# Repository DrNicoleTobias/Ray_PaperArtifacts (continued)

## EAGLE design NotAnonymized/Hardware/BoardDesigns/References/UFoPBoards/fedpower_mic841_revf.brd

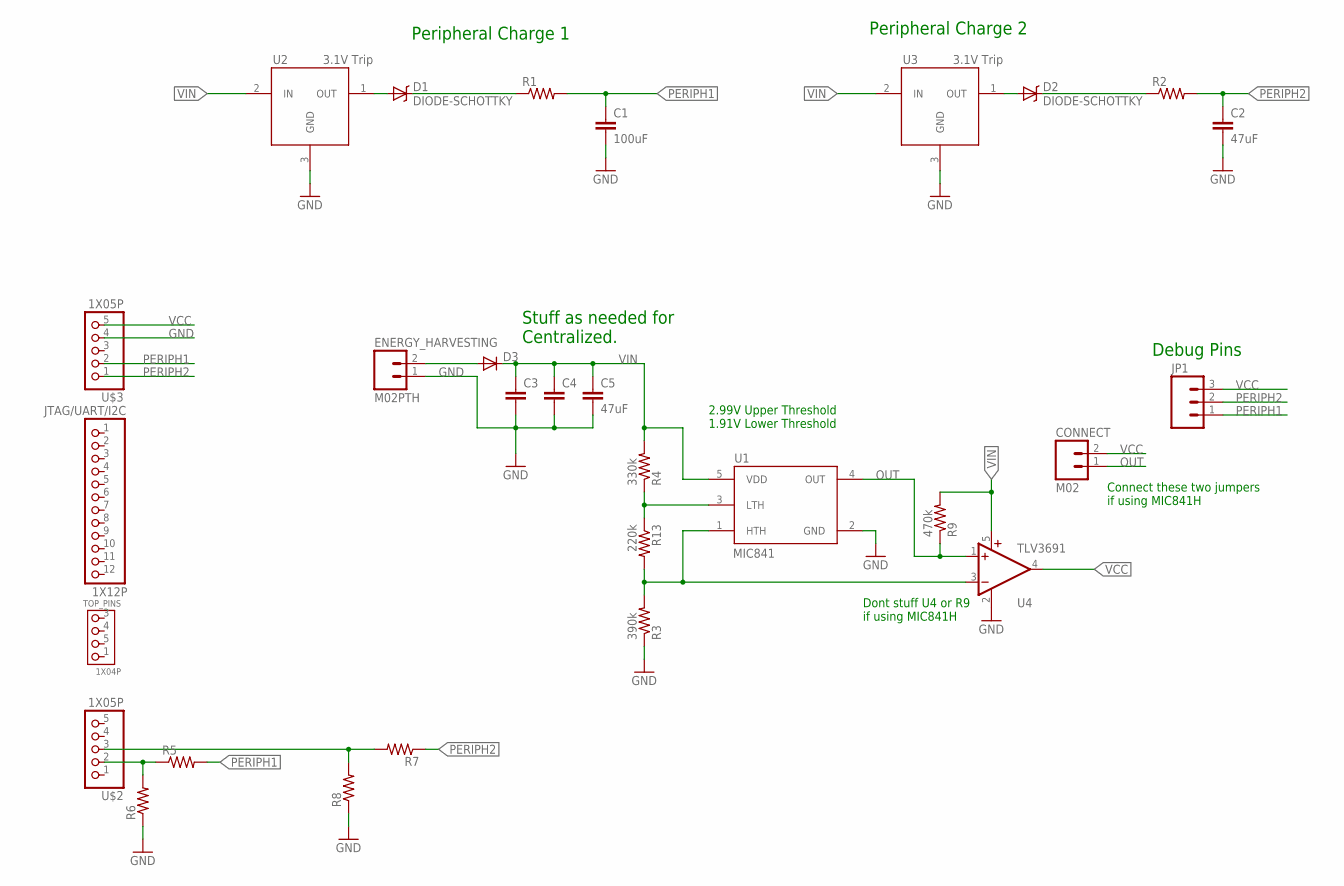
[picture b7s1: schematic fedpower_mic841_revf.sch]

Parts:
C1: 100uF; 0805
C2, C5: 47uF; 0805
C3, C4: 1.0UF-25V-+80/-20(0805); 0805
CONNECT: M02; 1X02-1.27MM
D1, D2: DIODE-SCHOTTKY; SOD-323
D3: DIODESOD; SOD-323
ENERGY_HARVESTING: M02PTH; 1X02
JP1: M03PTH; 1X03
JTAG/UART/I2C: 1X12P
R1, R2, R5, R6, R7, R8: 0.3OHM-1/8W-1%(0805); 0805
R3: 390k; 0805
R4: 330k; 0805
R9: 470k; 0805
R13: 220k; 0805
TOP_PINS: 1X04P
U1: MIC841; SC70-5
U2, U3: 3.1V Trip; SOT-23-5_1PRIMARY
U4: TLV3691; SC70-5
U$2, U$3: 1X05P

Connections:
GND: C1.2, C2.2, C3.2, C4.2, C5.2, ENERGY_HARVESTING.1, R3.1, R6.1, R8.1, U1.2 (GND), U2.3 (GND), U3.3 (GND), U4.2 (GND), U$3.4
unnamed: D1.2 (A), U2.1 (OUT)
unnamed: R4.1, R13.1, U1.3 (LTH)
unnamed: D1.1 (C), R1.1
unnamed: D2.2 (A), U3.1 (OUT)
unnamed: D3.2 (A), ENERGY_HARVESTING.2
unnamed: D2.1 (C), R2.1
unnamed: R3.2, R13.2, U1.1 (HTH), U4.3 (-IN)
OUT: CONNECT.1, R9.1, U1.4 (OUT), U4.1 (+IN)
P1.3/C3: R5.1, R6.2, U$2.2
P1.4/C4: R7.2, R8.2, U$2.3
PERIPH1: C1.1, JP1.1, R1.2, R5.2, U$3.2
PERIPH2: C2.1, JP1.2, R2.2, R7.1, U$3.1
VCC: CONNECT.2, JP1.3, U4.4 (OUT), U$3.5
VIN: C3.1, C4.1, C5.1, D3.1 (C), R4.2, R9.2, U1.5 (VDD), U2.2 (IN), U3.2 (IN), U4.5 (V+)

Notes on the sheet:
Peripheral Charge 1
Peripheral Charge 2
Debug Pins
Stuff as needed for Centralized.
Dont stuff U4 or R9 if using MIC841H
Connect these two jumpers if using MIC841H
2.99V Upper Threshold 1.91V Lower Threshold

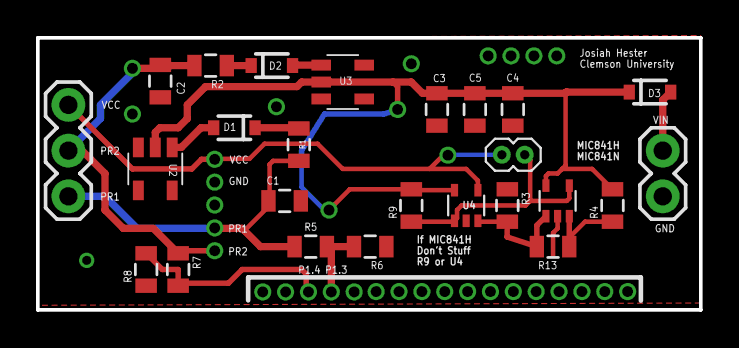
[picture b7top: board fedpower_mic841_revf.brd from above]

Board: 2 copper layers, 36.8 x 15.1 mm, 29 parts (0 on the bottom side), 15 nets.

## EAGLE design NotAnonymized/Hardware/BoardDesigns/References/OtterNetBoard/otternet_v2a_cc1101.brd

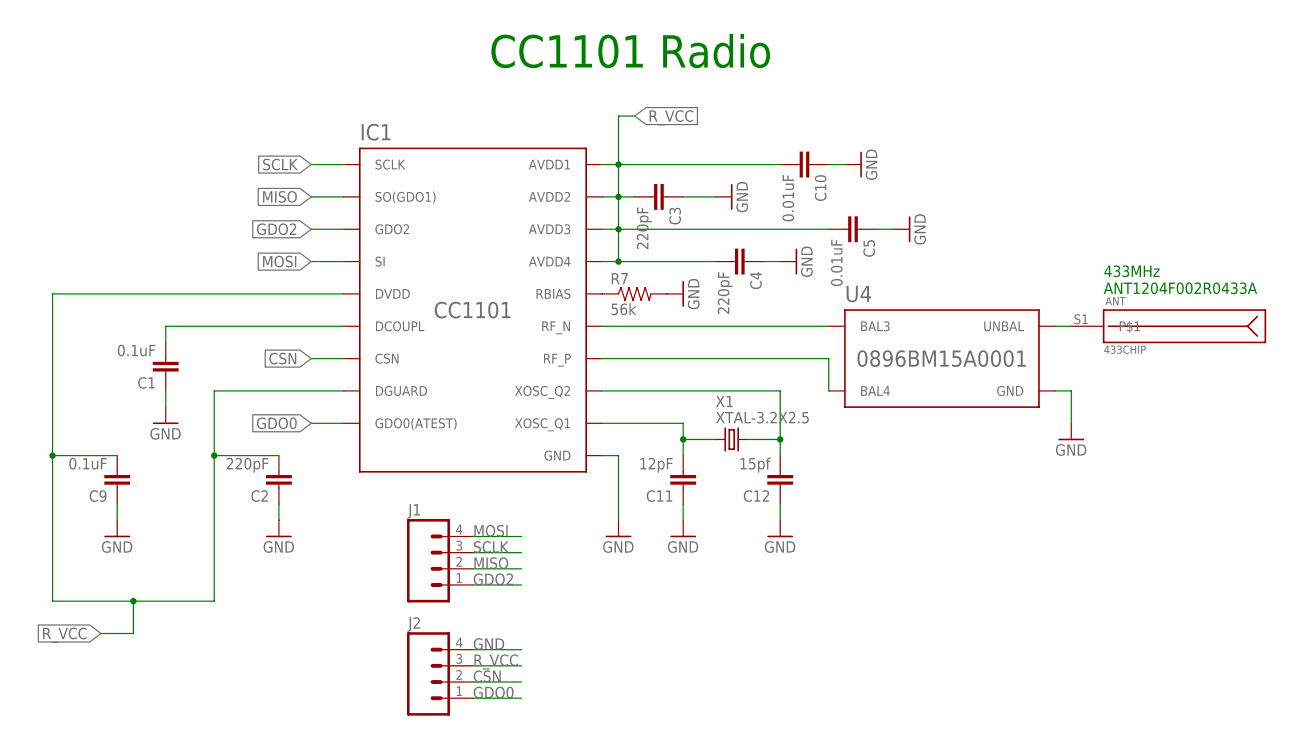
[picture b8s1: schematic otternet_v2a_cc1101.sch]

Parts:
ANT: 433CHIP; ANT-433-USP; MOUSER 603-ANT1204F002R0433
C1, C9: 0.1uF; 0402; MOUSER 581-530L104KT16T
C2, C3, C4: 220pF; 0402; MOUSER 605-500X07W221MV4T
C5, C10: 0.01uF; 0402; MOUSER 80-C0402T103K5RCL
C11: 12pF; 0402; MOUSER 581-04025U120FAT2A
C12: 15pf; 0402; MOUSER 80-CBR04C150F1GAC
IC1: CC1101; QLP20; DIGIKEY 296-35718-1-ND
J1, J2: M04PTH; 1X04
R7: 56k; 0402; DIGIKEY 311-56KJRCT-ND
U4: 0896BM15A0001; XXXXBM15A0001; MOUSER 609-0433BM15A0001E
X1: XTAL-3.2X2.5; DIGIKEY 644-1261-1-ND

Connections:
CSN: IC1.7 (CSN), J2.2
GDO0: IC1.6 (GDO0(ATEST)), J2.1
GDO2: IC1.3 (GDO2), J1.1
GND: C1.1, C2.1, C3.1, C4.1, C5.1, C9.1, C10.1, C11.1, C12.1, IC1.16 (GND), IC1.19 (GND), IC1.GND, IC1.GND1 (GND), IC1.GND2 (GND), IC1.GND3 (GND), IC1.GND4 (GND), IC1.GND5 (GND), J2.4, R7.2, U4.2 (GND), U4.5 (GND), U4.6 (GND)
MISO: IC1.2 (SO(GDO1)), J1.2
MOSI: IC1.20 (SI), J1.4
unnamed: IC1.17 (RBIAS), R7.1
unnamed: C12.2, IC1.10 (XOSC_Q2), X1.3 (2)
unnamed: IC1.12 (RF_P), U4.4 (BAL4)
unnamed: C1.2, IC1.5 (DCOUPL)
unnamed: IC1.13 (RF_N), U4.3 (BAL3)
unnamed: C11.2, IC1.8 (XOSC_Q1), X1.1
unnamed: ANT.S1, U4.1 (UNBAL)
R_VCC: C2.2, C3.2, C4.2, C5.2, C9.2, C10.2, IC1.4 (DVDD), IC1.9 (AVDD1), IC1.11 (AVDD2), IC1.14 (AVDD3), IC1.15 (AVDD4), IC1.18 (DGUARD), J2.3
SCLK: IC1.1 (SCLK), J1.3

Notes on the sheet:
433MHz ANT1204F002R0433A
CC1101 Radio

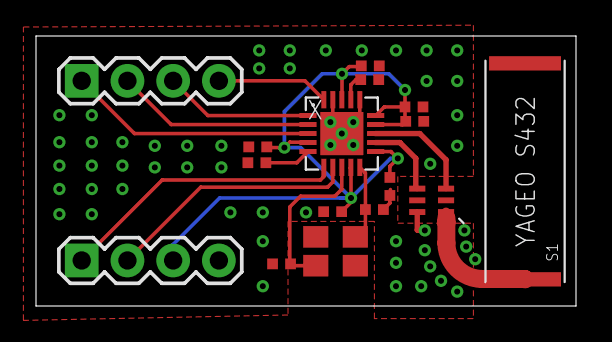
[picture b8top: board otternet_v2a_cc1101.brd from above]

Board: 2 copper layers, 30.0 x 15.0 mm, 16 parts (0 on the bottom side), 15 nets.

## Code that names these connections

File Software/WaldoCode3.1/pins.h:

#ifndef PINS_h
#define PINS_h

/* ------------------------------------------------------------------------------------------------
 *                                      GDO0 Pin Configuration
 * ------------------------------------------------------------------------------------------------
 */
#define GDO0_BIT__                     0
#define GDO0_PORT__                    6
#define CONFIG_GDO0_PIN_AS_INPUT()       st( INFIX( P, GDO0_PORT__, SEL0 ) &= ~BV(GDO0_BIT__); INFIX( P, GDO0_PORT__, DIR ) &= ~BV(GDO0_BIT__); ) /* clear pin special function default */
#define GDO0_PIN_IS_HIGH()               ( INFIX( P, GDO0_PORT__, IN ) & BV(GDO0_BIT__))


#define GDO0_INT_VECTOR                  INFIX( PORT, GDO0_PORT__, _VECTOR )
#define ENABLE_GDO0_INT()                st( INFIX( P, GDO0_PORT__, IE )  |=  BV(GDO0_BIT__); ) /* atomic operation */
#define DISABLE_GDO0_INT()               st( INFIX( P, GDO0_PORT__, IE )  &= ~BV(GDO0_BIT__); ) /* atomic operation */
#define GDO0_INT_IS_ENABLED()             (  INFIX( P, GDO0_PORT__, IE )  &   BV(GDO0_BIT__) )
#define CLEAR_GDO0_INT_FLAG()            st( INFIX( P, GDO0_PORT__, IFG ) &= ~BV(GDO0_BIT__); ) /* atomic operation */
#define GDO0_INT_FLAG_IS_SET()            (  INFIX( P, GDO0_PORT__, IFG ) &   BV(GDO0_BIT__) )
#define CONFIG_GDO0_RISING_EDGE_INT()    st( INFIX( P, GDO0_PORT__, IES ) &= ~BV(GDO0_BIT__); ) /* atomic operation */
#define CONFIG_GDO0_FALLING_EDGE_INT()   st( INFIX( P, GDO0_PORT__, IES ) |=  BV(GDO0_BIT__); ) /* atomic operation */


/* ------------------------------------------------------------------------------------------------
 *                                      GDO2 Pin Configuration
 * ------------------------------------------------------------------------------------------------
 */
#define GDO2_BIT__                     5
#define GDO2_PORT__                    1
#define CONFIG_GDO2_PIN_AS_INPUT()       st( INFIX( P, GDO2_PORT__, SEL0 ) &= ~BV(GDO2_BIT__); INFIX( P, GDO2_PORT__, DIR ) &= ~BV(GDO2_BIT__);) /* clear pin special function default */
#define GDO2_PIN_IS_HIGH()               ( INFIX( P, GDO2_PORT__, IN ) & BV(GDO2_BIT__))

#define GDO2_INT_VECTOR                  INFIX( PORT, GDO2_PORT__, _VECTOR )
#define ENABLE_GDO2_INT()                st( INFIX( P, GDO2_PORT__, IE )  |=  BV(GDO2_BIT__); ) /* atomic operation */
#define DISABLE_GDO2_INT()               st( INFIX( P, GDO2_PORT__, IE )  &= ~BV(GDO2_BIT__); ) /* atomic operation */
#define GDO2_INT_IS_ENABLED()             (  INFIX( P, GDO2_PORT__, IE )  &   BV(GDO2_BIT__) )
#define CLEAR_GDO2_INT_FLAG()            st( INFIX( P, GDO2_PORT__, IFG ) &= ~BV(GDO2_BIT__); ) /* atomic operation */
#define GDO2_INT_FLAG_IS_SET()            (  INFIX( P, GDO2_PORT__, IFG ) &   BV(GDO2_BIT__) )
#define CONFIG_GDO2_RISING_EDGE_INT()    st( INFIX( P, GDO2_PORT__, IES ) &= ~BV(GDO2_BIT__); ) /* atomic operation */
#define CONFIG_GDO2_FALLING_EDGE_INT()   st( INFIX( P, GDO2_PORT__, IES ) |=  BV(GDO2_BIT__); ) /* atomic operation */


/* ------------------------------------------------------------------------------------------------
 *                                      SPI Configuration
 * ------------------------------------------------------------------------------------------------
 */

/* CSn Pin Configuration */
#define SPI_CSN_GPIO_BIT__             3
#define SPI_CONFIG_CSN_PIN_AS_OUTPUT()   st( P6DIR |=  BV(SPI_CSN_GPIO_BIT__); )
#define SPI_DRIVE_CSN_HIGH()             st( P6OUT |=  BV(SPI_CSN_GPIO_BIT__); ) /* atomic operation */
#define SPI_DRIVE_CSN_LOW()              st( P6OUT &= ~BV(SPI_CSN_GPIO_BIT__); ) /* atomic operation */
#define SPI_CSN_IS_HIGH()                 (  P6OUT &   BV(SPI_CSN_GPIO_BIT__) )

/* SCLK Pin Configuration */
#define SPI_SCLK_GPIO_BIT__            4
#define SPI_CONFIG_SCLK_PIN_AS_OUTPUT()  st( P1DIR |=  BV(SPI_SCLK_GPIO_BIT__); )
#define SPI_DRIVE_SCLK_HIGH()            st( P1OUT |=  BV(SPI_SCLK_GPIO_BIT__); )
#define SPI_DRIVE_SCLK_LOW()             st( P1OUT &= ~BV(SPI_SCLK_GPIO_BIT__); )

/* SI Pin Configuration */
#define SPI_SI_GPIO_BIT__              6
#define SPI_CONFIG_SI_PIN_AS_OUTPUT()    st( P1DIR |=  BV(SPI_SI_GPIO_BIT__); )
#define SPI_DRIVE_SI_HIGH()              st( P1OUT |=  BV(SPI_SI_GPIO_BIT__); )
#define SPI_DRIVE_SI_LOW()               st( P1OUT &= ~BV(SPI_SI_GPIO_BIT__); )

/* SO Pin Configuration */
#define SPI_SO_GPIO_BIT__              7
#define SPI_CONFIG_SO_PIN_AS_INPUT()     st( P1DIR &= ~BV(SPI_SO_GPIO_BIT__);)
#define SPI_SO_IS_HIGH()                 ( P1IN & BV(SPI_SO_GPIO_BIT__) )

/* SPI Port Configuration */
#define SPI_CONFIG_PORT()                st( P1SEL0 |= BV(SPI_SI_GPIO_BIT__)   |  \
                                                           BV(SPI_SO_GPIO_BIT__); \
                                              P1SEL1 &= ~(BV(SPI_SI_GPIO_BIT__) | BV(SPI_SO_GPIO_BIT__)); \
                                                  P1SEL0 |= BV(SPI_SCLK_GPIO_BIT__); \
                                                  P1SEL1 &= ~BV(SPI_SCLK_GPIO_BIT__); )

#define SPI_INIT() \
st ( \
  UCB0CTLW0 |= UCSWRST;                           \
  UCB0CTLW0 |= UCSWRST | UCSSEL_2;                 \
  UCB0CTLW0 |= UCCKPH | UCMSB | UCMST | UCSYNC;   \
  UCB0BR0  = 0x02;                                 \
  UCB0BR1  = 0;                                 \
  SPI_CONFIG_PORT();                       \
  UCB0CTLW0 &= ~UCSWRST;                         \
)

/* read/write macros */
#define SPI_WRITE_BYTE(x)                st( UCB0IFG &= ~UCRXIFG;  UCB0TXBUF = x; )
#define SPI_READ_BYTE()                  UCB0RXBUF
#define SPI_WAIT_DONE()                  while(!(UCB0IFG & UCRXIFG));

#endif

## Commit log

2024-04-25 Update README.md
    attempting an update to the readme to test out the anonymous repo thingy
2024-04-26 Initial Pass for CleanUp
2024-04-30 pcb pdfs
2024-04-30 Update with ReadMe
2024-04-30 Needed words
2024-05-01 updates to readme
2024-05-01 Updating Readme and train model code
2024-05-01 now will you be an image?
2024-05-01 maybe this time!
2024-05-01 again?
2024-05-01 still trying
2024-05-01 maybe now?
2024-05-01 last time maybe
2024-05-01 undoing last change
2024-05-01 Updating folder structure
2024-05-01 Updating how to build text
2024-05-01 Hardware ReadMes done
2024-05-01 Cleaning up folder and Updating Readme. Hardware Folder done
2024-05-01 does this look better?
2024-05-01 Moving text around
2024-05-01 adding pics
2024-05-01 edit
2024-05-01 edit again
2024-05-01 pushing updates...
2024-05-01 Controlled Exp Code and ReadMes
2024-05-01 Updating readMes and Uncontrolled files
2024-05-01 Removing folder
2024-05-01 Final Update as I crash
2024-05-01 last last update
2024-05-01 make look better
2024-05-01 maybe?
2024-05-01 how about now?
2024-05-01 Adding in changes
2024-05-01 all the text
2024-05-14 Updating Repo Review Folder with Demo Video
2024-05-14 Adding sample controlled data and summaries for ITW table
2024-05-14 Updating main readme
2024-05-14 fixing broken figure links
2024-05-14 layout fix
2024-05-14 moving previous text to where it makes sense with new folder structure
2024-05-14 Added Table for reference
2024-05-14 Adding Summary Table Pics for Information gathered at each location
2024-05-14 Adding Data Excel files (Only modification to the files since creation is adding labels to the table columns)
2024-05-14 Adding visual aid for uncontrolled experiments
2024-05-16 adding samples of manual matching sensor data to ground truth
2024-05-16 adding readme for reviewers
2024-05-16 Updating images
2024-05-16 readme fix
2024-05-16 correcting file extensions
2024-05-16 Update description for controlled sample file
2024-05-16 trying to embed video
2024-05-16 video fix?
2024-05-16 fixed yet?
2024-05-16 trying to unbreak it
